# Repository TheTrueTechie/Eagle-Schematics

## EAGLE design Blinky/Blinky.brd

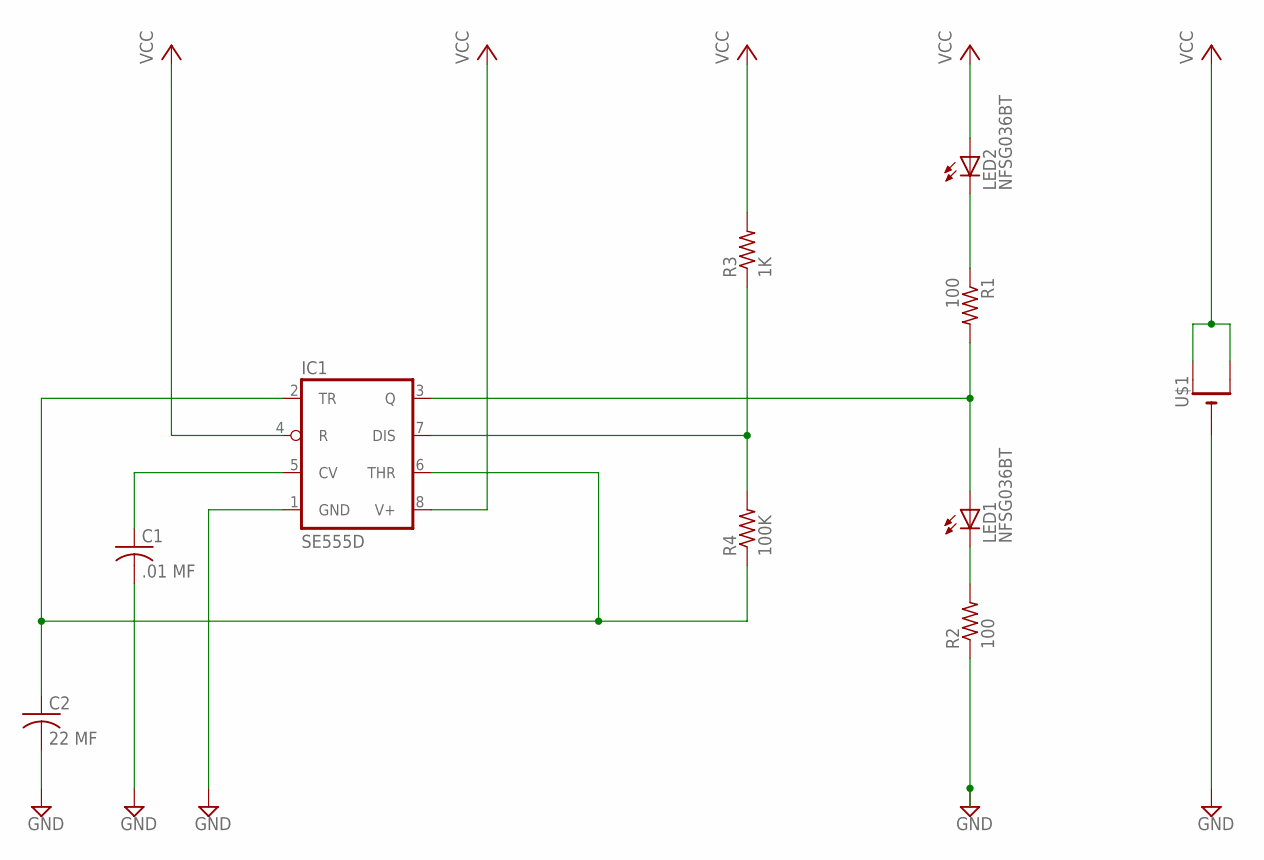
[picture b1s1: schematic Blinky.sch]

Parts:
C1: .01 MF; C0805; MPN 885012007009
C2: 22 MF; C0805; MPN GRT21BR60J226ME13L
IC1: SE555D; SO08; MPN TLC555CDR
LED1, LED2: NFSG036BT; MPN KPTD-2012ZGCK
R1, R2: 100; M0805; MPN MCTF0805BTC1000
R3: 1K; M0805; MPN CRCW08051K00FKTA
R4: 100K; M0805; MPN CRCW0805100KFKTA
U$1: CR1220THM; CR1220-THM; MPN 500

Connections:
GND: C1.2, C2.2, IC1.1 (GND), R2.1, U$1.-
unnamed: C1.1, IC1.5 (CV)
unnamed: IC1.7 (DIS), R3.1, R4.2
unnamed: IC1.3 (Q), LED1.A, R1.2
unnamed: LED1.C, R2.2
unnamed: LED2.C, R1.1
unnamed: C2.1, IC1.2 (TR), IC1.6 (THR), R4.1
VCC: IC1.4 (R), IC1.8 (V+), LED2.A, R3.2, U$1.+1 (+), U$1.+2 (+1)

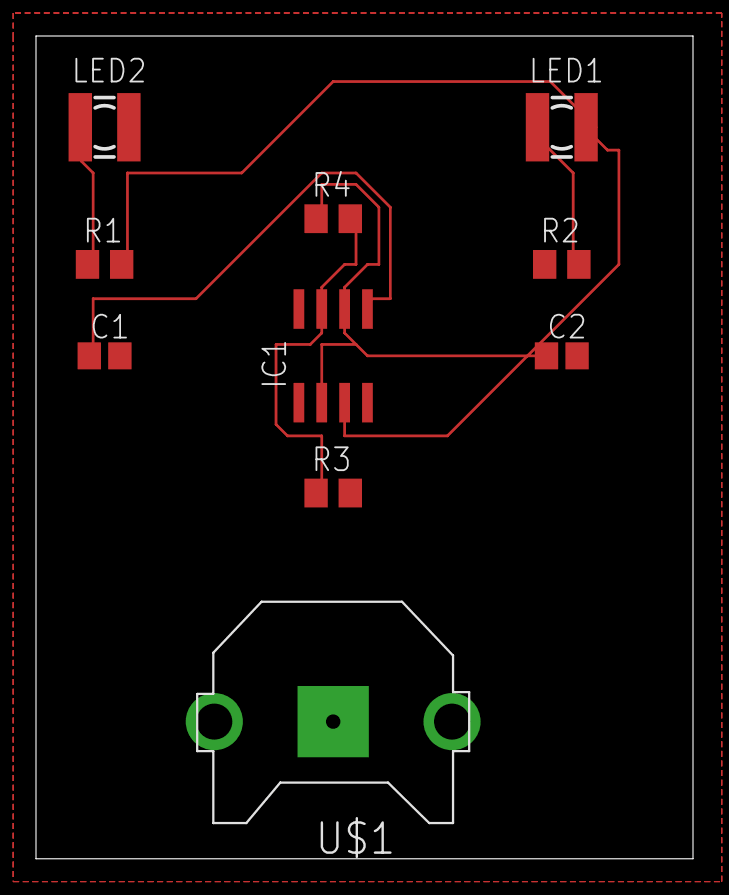
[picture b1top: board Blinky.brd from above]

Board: 2 copper layers, 36.5 x 45.7 mm, 10 parts (0 on the bottom side), 8 nets.

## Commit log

2018-02-24 Blinky
    Almost done with Blinky Schematics
